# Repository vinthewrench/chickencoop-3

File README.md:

# Chicken Coop Controller 3.0

**Build your own automated, off-grid chicken coop door**

A minimal, ultra-reliable, battery-powered AVR controller that opens the door at sunrise, closes and locks it at sunset — completely offline, no sensors, no Wi-Fi, no cloud, no GPS.

Designed for a mobile pasture-raised coop that moves with cattle and sheep. Runs for months on a small 12 V battery (solar is only a top-up). Survives Arkansas mud, ice, dust, coyotes, and power failures.

Full 18-page design story, sunrise math, and lessons learned here:  
https://www.vinthewrench.com/<update this>

### Features

- True sunrise/sunset calculation using location + date (NO light sensor)
- Gravity-hung door with Progressive Automations PA-14 actuator
- Automatic locking bar (automotive-style actuator) to stop predators
- Manual override button with bi-color LED status
- Ultra-low sleep current (~355 µA) → months on a 7–22 Ah SLA/AGM battery
- One-time setup via serial console (no phone app or internet required)
- Two extra latching relays for electric fence or lights (zero holding current)
- Handles power failures, manual overrides, and reboots correctly
- Fully open-source (firmware + schematics + PCB)

### Licenses

- Firmware: MIT
- Hardware (schematics + PCB): CERN-OHL-P v2

You are free to study, modify, and build your own.

---

## How It Works

1. The DS3231M RTC wakes the ATmega1284P at the next event (sunrise or sunset).
2. Firmware calculates exact sunrise/sunset from latitude, longitude, and date.
3. If needed, it drives the door actuator and lock.
4. It sets the next alarm and goes back to deep sleep.

No drift, no false triggers from clouds, headlights, or moving the coop.

Manual button press overrides the schedule until the next natural event (sunrise/sunset). The system never fights you.

---

## Hardware

Custom 100 × 130 mm PCB (all through-hole friendly where possible).

### Major Components

| Component        | Part                          | Notes                                         |
| ---------------- | ----------------------------- | --------------------------------------------- |
| MCU              | ATmega1284P-PU (DIP-40)       | 128 KB flash, easy ISP, repairable            |
| RTC              | DS3231M                       | Integrated resonator, temperature compensated |
| Door Actuator    | Progressive Automations PA-14 | IP65, internal limits, stainless rod          |
| Lock Actuator    | 12 V automotive door lock     | Pulses only (200–300 ms)                      |
| Motor Drivers    | 2 × VNH7100BAS                | 15 A H-bridges with thermal copper pours      |
| 5 V Regulator    | Pololu D24V22F5               | High efficiency, low quiescent current        |
| Button           | Illuminated bi-color switch   | Red/Green status + override                   |
| Relays           | 2 × DSP1-L2-DC12V             | Latching (zero holding current)               |
| Relay Driver     | ULN2003A                      | Drives relays + optional loads                |
| Optional Console | SparkFun DEV-15096            | USB-to-serial for setup (removable)           |

Power: Single 12 V battery (SLA/AGM recommended). Direct 12 V to motors, regulated 5 V for logic.

---

## Firmware

Written in plain C for avr-gcc. No Arduino framework, no hidden magic.

Typical workflow:

```bash
cd firmware
make set-fuses
make
make flash          # or use your programmer
```

Full build system, clean targets, and EEPROM config handling included.

---

## Setup & Configuration

1. Flip the **CONFIG switch** to ON (this puts the controller into console mode).
2. Connect the optional SparkFun USB-to-serial module (or any 5 V TTL serial).
3. Open a terminal (38400 baud).
4. Set date/time, latitude, longitude, timezone offset, and schedule offsets.
5. Flip the **CONFIG switch** back to OFF when done.
6. Remove the module — the controller no longer needs it.

All settings stored in EEPROM. No re-configuration unless you move to a new location.

---

## Using the CONFIG Switch & Console

The physical **CONFIG switch** on the board toggles between normal low-power run mode and console configuration mode. When flipped to ON, the MCU stays awake, enables the serial console, and allows full setup/debug without sleeping. Flip back to OFF to resume automatic scheduling and deep sleep.

**Configuration steps:**

1. Flip CONFIG to ON.
2. Connect serial (38400 baud) and type commands.
3. Use `set` to configure, `event add` for schedules, `save` to commit.
4. Flip CONFIG to OFF.

**What you need to set (minimum for basic operation):**

- Date and time (`set date YYYY-MM-DD`, `set time HH:MM[:SS]`)
- Location (`set lat +/-DD.DDDD`, `set lon +/-DDD.DDDD`)
- Timezone (`set tz +/-HH`, `set dst on|off`)
- Events (`event add door on sunrise +0`, `event add door off sunset -15`, etc. for lock/relays)

**Key commands:**
| Command | What it does |
|----------------------------------|--------------|
| `help` | List all commands |
| `config` | Show current settings |
| `set date YYYY-MM-DD` | Set date |
| `set time HH:MM[:SS]` | Set time (local) |
| `set lat +/-DD.DDDD` | Set latitude |
| `set lon +/-DDD.DDDD` | Set longitude |
| `set tz +/-HH` | Set timezone offset |
| `set dst on\|off` | Enable/disable DST |
| `event add ...` | Add door open/close events (sunrise/sunset or fixed time) |
| `save` | Commit everything to EEPROM |
| `schedule` | Show today’s full schedule |
| `solar` | Show sunrise/sunset |
| `door open\|close\|toggle` | Manual door test |
| `lock engage\|release` | Manual lock test |

Type `help` for full list. Changes are RAM-only until `save`.

---

## Repository Contents

- /firmware/ — AVR source + Makefile
- /hardware/ — KiCad schematics + PCB layout

---

## Typical Daily Workflow (after initial setup)

The controller just works. You walk out once a day to collect eggs.

---

## Links & Resources

- Full article: https://www.vinthewrench.com/<update>
- Buy the exact actuator: Progressive Automations PA-14 (PA-01-12-56-N-12VDC model)

Questions? Open an issue or find me on X @vinthewrench.

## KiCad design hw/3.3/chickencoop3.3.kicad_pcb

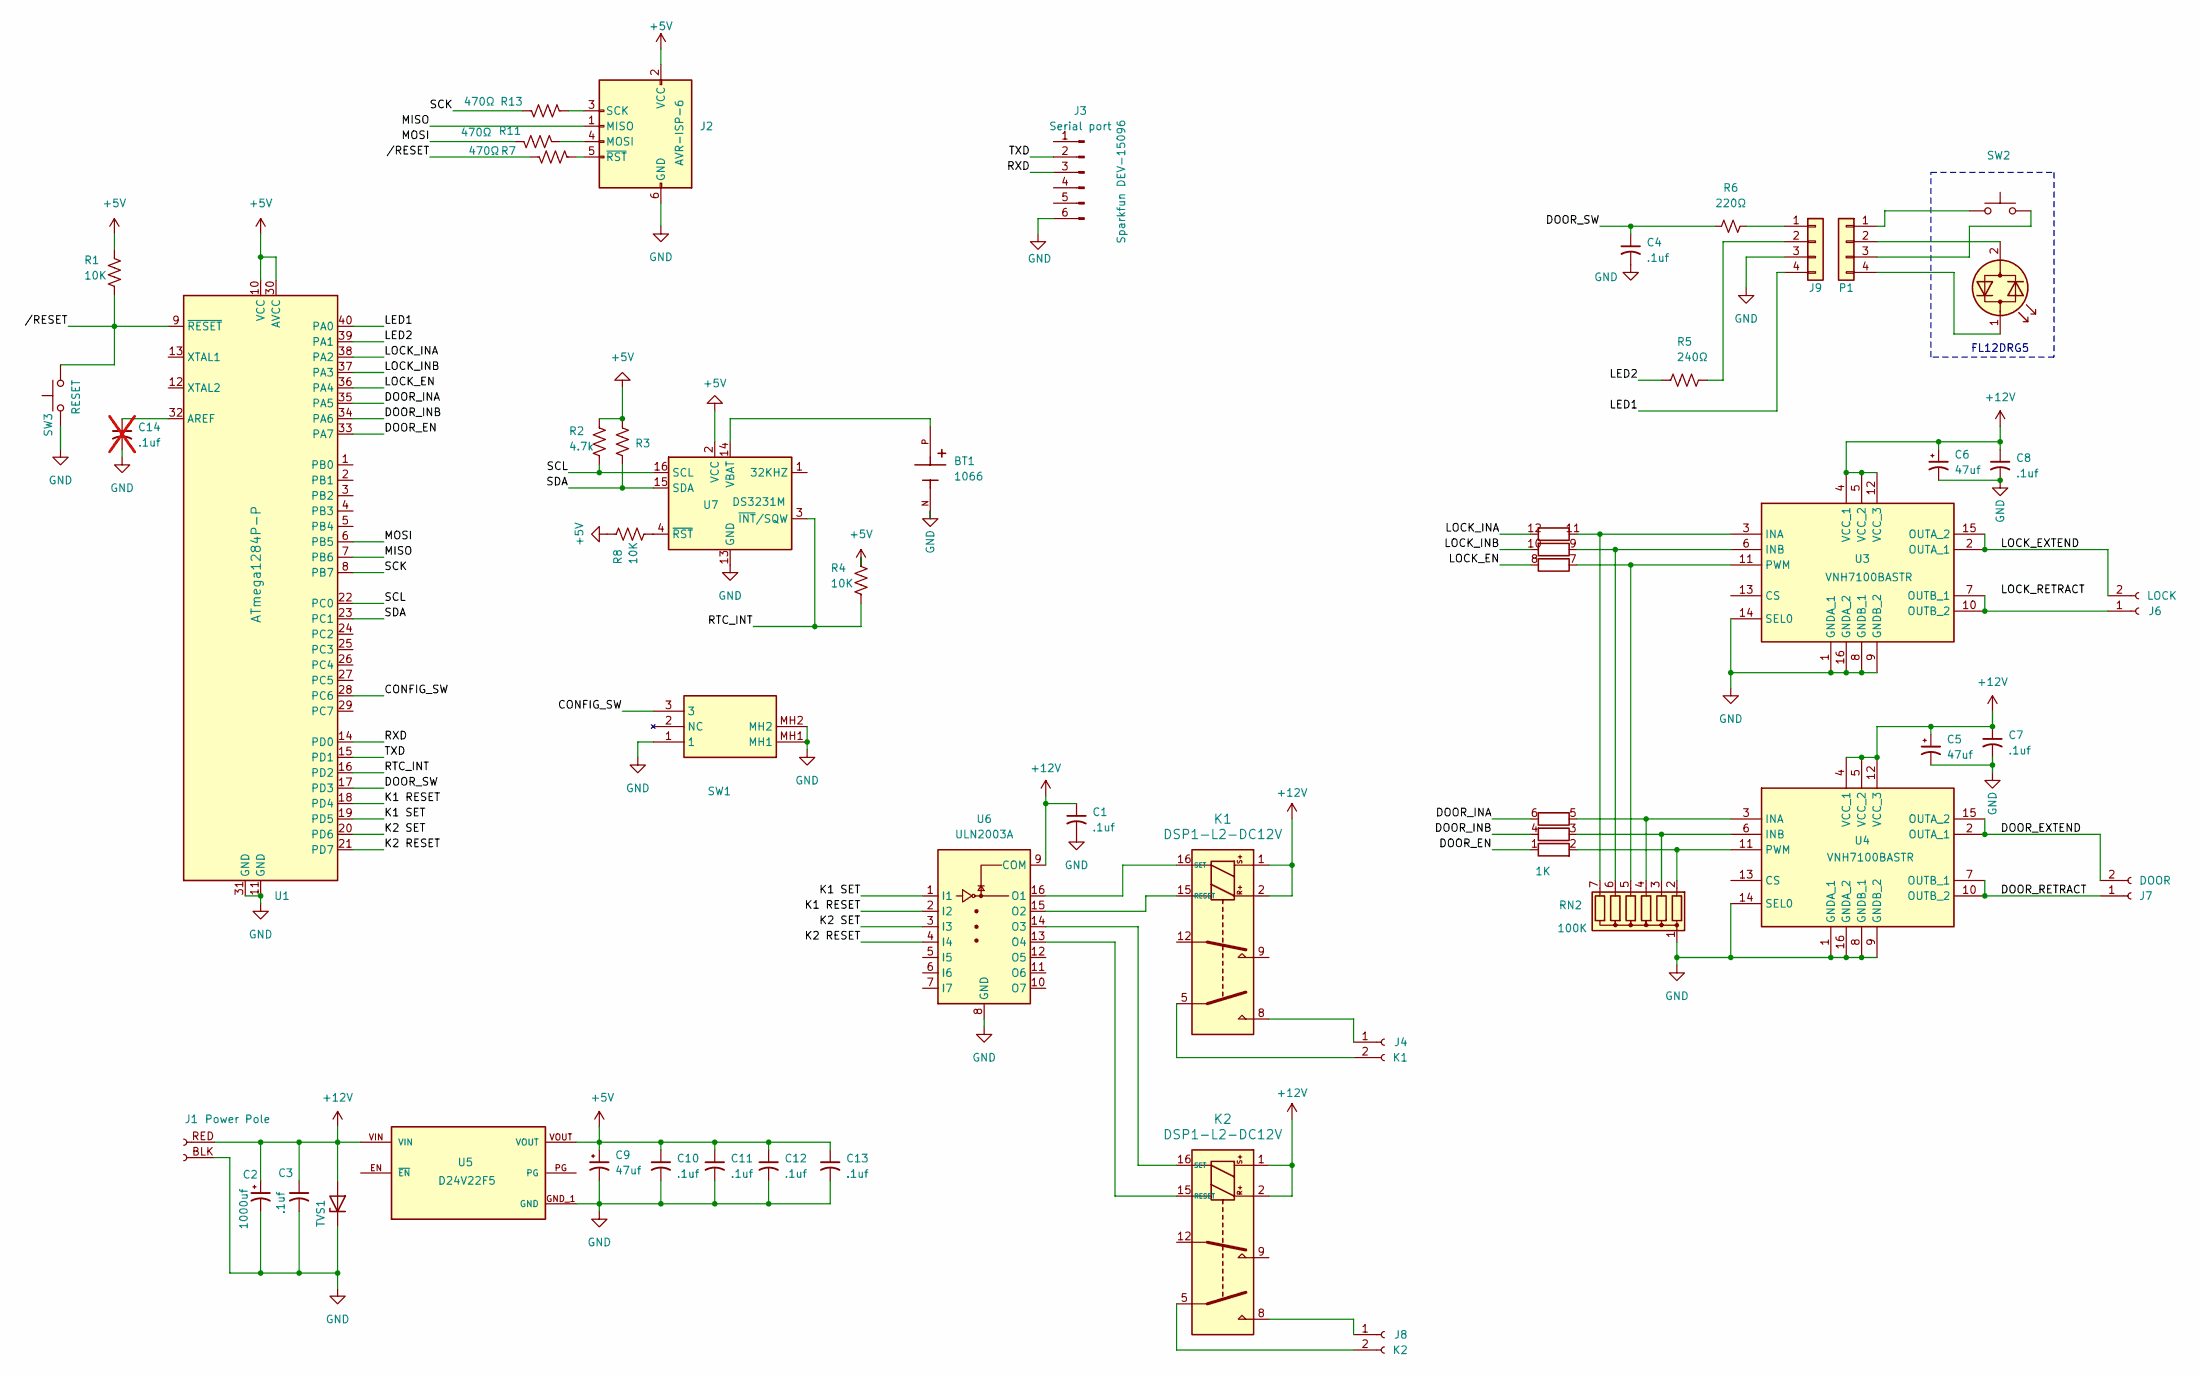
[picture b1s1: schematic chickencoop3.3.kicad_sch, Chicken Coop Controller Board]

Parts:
BT1: 1066; BAT_1066; PARTREV E
C1, C3, C4, C7, C8, C10, C11, C12, C13: .1uf; RCER71H104K0DBH03A
C2: 1000uf; CP_Radial_D10.0mm_P5.00mm
C5, C6, C9: 47uf; CP_Radial_D5.0mm_P2.00mm
C14: .1uf; RCER71H104K0DBH03A; not fitted
D1: LED_Dual_Bidirectional
J1: Power Pole; powerpole
J2: AVR-ISP-6; PinHeader_2x03_P2.54mm_Vertical
J3: Serial port; PinHeader_1x06_P2.54mm_Vertical
J4: K1; TerminalBlock_Phoenix_MKDS-1,5-2-5.08_1x02_P5.08mm_Horizont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
J6: LOCK; TerminalBlock_Phoenix_MKDS-1,5-2-5.08_1x02_P5.08mm_Horizont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
J7: DOOR; TerminalBlock_Phoenix_MKDS-1,5-2-5.08_1x02_P5.08mm_Horizont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
J8: K2; TerminalBlock_Phoenix_MKDS-1,5-2-5.08_1x02_P5.08mm_Horizont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
J9: Mini‑Fit Jr; Molex_Mini-Fit_Jr_5566-04A_2x02_P4.20mm_Vertical
K1, K2: DSP1-L2-DC12V
P1: Mini‑Fit Jr; Molex_Mini-Fit_Jr_5566-04A_2x02_P4.20mm_Vertical
R1, R4, R8: 10K; R_Axial_DIN0204_L3.6mm_D1.6mm_P7.62mm_Horizontal
R2: 4.7k; R_Axial_DIN0204_L3.6mm_D1.6mm_P7.62mm_Horizontal
R3: 4.7K; R_Axial_DIN0204_L3.6mm_D1.6mm_P7.62mm_Horizontal
R5: 240Ω; R_Axial_DIN0204_L3.6mm_D1.6mm_P7.62mm_Horizontal
R6: 220Ω; R_Axial_DIN0204_L3.6mm_D1.6mm_P7.62mm_Horizontal
R7, R11, R13: 470Ω; R_Axial_DIN0204_L3.6mm_D1.6mm_P7.62mm_Horizontal
RN2: 100K; R_Array_SIP7; Manufacturer_Part_Number 4607X-101-104LF
RN4: 1K; R_Array_SIP12; Manufacturer_Part_Number 4612X-102-102LF
SW1: SW_SPST; AS11CH; Mouser Part Number 633-AS11CH
SW2: SW_Push
SW3: RESET; SW_PUSH_6mm
TVS1: P6SMB18A; D_SMB_Handsoldering
U1: ATmega1284P-P; DIP-40_W15.24mm
U3, U4: VNH7100BASTR; SOIC127P600X175-16N; Manufacturer_Part_Number VNH7100BASTR; Mouser Part Number 511-VNH7100BASTR
U5: D24V22F5; MODULE_5V_2.5A_STEP-DOWN_D24V22F5; PARTREV 12 November 2015
U6: ULN2003A; DIP-16_W7.62mm
U7: DS3231M; SOIC-16W_7.5x10.3mm_P1.27mm

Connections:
+5V: C9.1, C10.1, C11.1, C12.1, C13.1, J2.2 (VCC), R1.1, R2.1, R3.1, R4.1, R8.1, U1.10 (VCC), U1.30 (AVCC), U5.VOUT, U7.2 (VCC)
+12V: C1.1, C2.1, C3.1, C5.1, C6.1, C7.1, C8.1, J1.RED, K1.1, K1.2, K2.1, K2.2, TVS1.2 (A), U3.4 (VCC_1), U3.5 (VCC_2), U3.12 (VCC_3), U4.4 (VCC_1), U4.5 (VCC_2), U4.12 (VCC_3), U5.VIN, U6.9 (COM)
/CONFIG_SW: SW1.3, U1.28 (PC6)
/DOOR_EN: RN4.1 (R1.1), U1.33 (PA7)
/DOOR_EXTEND: J7.2, U4.2 (OUTA_1), U4.15 (OUTA_2)
/DOOR_INA: RN4.6 (R3.2), U1.35 (PA5)
/DOOR_INB: RN4.4 (R2.2), U1.34 (PA6)
/DOOR_RETRACT: J7.1, U4.7 (OUTB_1), U4.10 (OUTB_2)
/DOOR_SW: C4.1, R6.1, U1.17 (PD3)
/K1 RESET: U1.18 (PD4), U6.2 (I2)
/K1 SET: U1.19 (PD5), U6.1 (I1)
/K2 RESET: U1.21 (PD7), U6.4 (I4)
/K2 SET: U1.20 (PD6), U6.3 (I3)
/LED1: J9.4, U1.40 (PA0)
/LED2: R5.1, U1.39 (PA1)
/LOCK_EN: RN4.8 (R4.2), U1.36 (PA4)
/LOCK_EXTEND: J6.2, U3.2 (OUTA_1), U3.15 (OUTA_2)
/LOCK_INA: RN4.12 (R6.2), U1.38 (PA2)
/LOCK_INB: RN4.10 (R5.2), U1.37 (PA3)
/MISO: J2.1 (MISO), U1.7 (PB6)
/MOSI: R11.1, U1.6 (PB5)
/RTC_INT: R4.2, U1.16 (PD2), U7.3 (~INT/SQW)
/RXD: J3.3, U1.14 (PD0)
/SCK: R13.1, U1.8 (PB7)
/SCL: R2.2, U1.22 (PC0), U7.16 (SCL)
/SDA: R3.2, U1.23 (PC1), U7.15 (SDA)
/TXD: J3.2, U1.15 (PD1)
//RESET: R1.2, R7.1, SW3.2, U1.9 (~RESET)
GND: BT1.N, C1.2, C2.2, C3.2, C4.2, C5.2, C6.2, C7.2, C8.2, C9.2, C10.2, C11.2, C12.2, C13.2, C14.2, J1.BLK, J2.6 (GND), J3.6, J9.3, RN2.1 (common), SW1.1, SW1.MH1, SW1.MH2, SW3.1, TVS1.1 (K), U1.11 (GND), U1.31 (GND), U3.1 (GNDA_1), U3.8 (GNDB_1), U3.9 (GNDB_2), U3.14 (SEL0), U3.16 (GNDA_2), U4.1 (GNDA_1), U4.8 (GNDB_1), U4.9 (GNDB_2), U4.14 (SEL0), U4.16 (GNDA_2), U5.GND_1 (GND), U5.GND_2 (GND), U6.8 (GND), U7.5 (GND), U7.6 (GND), U7.7 (GND), U7.8 (GND), U7.9 (GND), U7.10 (GND), U7.11 (GND), U7.12 (GND), U7.13 (GND)
unnamed: D1.1 (KA), P1.4
unnamed: D1.2 (AK), P1.2
unnamed: J2.4 (MOSI), R11.2
unnamed: J2.3 (SCK), R13.2
unnamed: J2.5 (~RST), R7.2
unnamed: J4.1, K1.8
unnamed: J4.2, K1.5
unnamed: J6.1, U3.7 (OUTB_1), U3.10 (OUTB_2)
unnamed: J8.1, K2.8
unnamed: J8.2, K2.5
unnamed: J9.1, R6.2
unnamed: J9.2, R5.2
unnamed: K1.15 (RESET), U6.15 (O2)
unnamed: K1.16 (SET), U6.16 (O1)
unnamed: K2.15 (RESET), U6.13 (O4)
unnamed: K2.16 (SET), U6.14 (O3)
unnamed: P1.1, SW2.1
unnamed: P1.3, SW2.2
unnamed: RN2.2 (R1), RN4.2 (R1.2), U4.11 (PWM)
unnamed: RN2.3 (R2), RN4.3 (R2.1), U4.6 (INB)
unnamed: RN2.4 (R3), RN4.5 (R3.1), U4.3 (INA)
unnamed: RN2.5 (R4), RN4.7 (R4.1), U3.11 (PWM)
unnamed: RN2.6 (R5), RN4.9 (R5.1), U3.6 (INB)
unnamed: RN2.7 (R6), RN4.11 (R6.1), U3.3 (INA)
unnamed: C14.1, U1.32 (AREF)
unnamed: BT1.P, U7.14 (VBAT)
unnamed: R8.2, U7.4 (~RST)

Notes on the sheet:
FL12DRG5

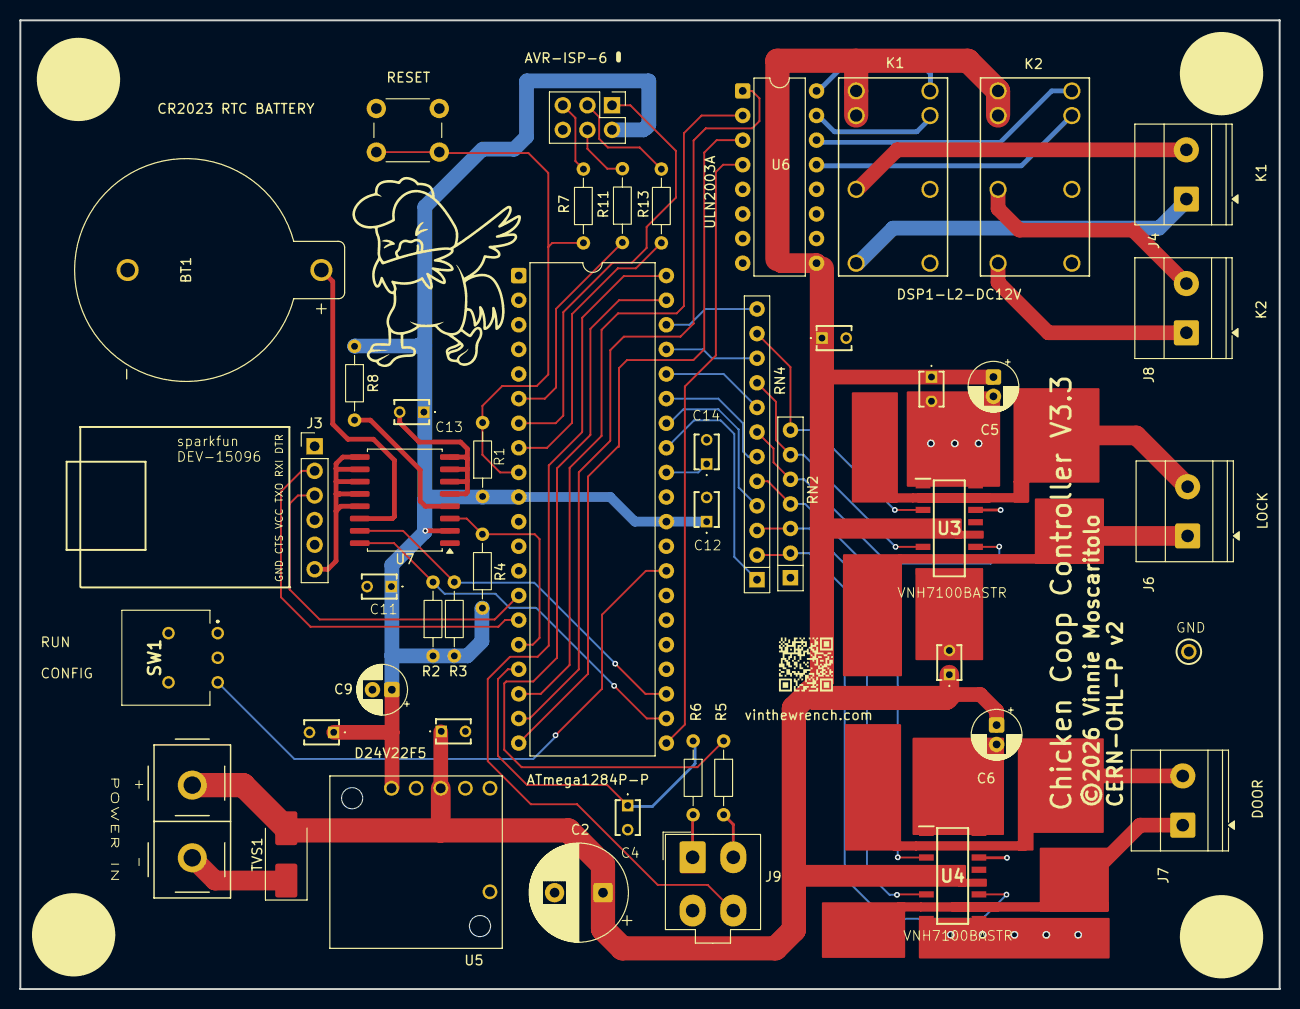
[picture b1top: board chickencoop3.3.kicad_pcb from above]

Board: 2 copper layers, 130.0 x 100.0 mm, 47 parts (0 on the bottom side), 52 nets.

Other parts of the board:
TP3: GND; 5000

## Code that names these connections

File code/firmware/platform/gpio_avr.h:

/*
 * gpio_avr.h
 *
 * Project: Chicken Coop Controller
 * Purpose: AVR GPIO pin definitions and low-level hardware mapping
 *
 * This header defines the canonical mapping between AVR GPIO pins
 * and physical hardware functions on the Chicken Coop Controller PCB.
 *
 * IMPORTANT DESIGN RULES:
 *  - All mappings in this file are LOCKED to the board schematic.
 *  - Do NOT rename, repurpose, or reassign any pin here unless
 *    the PCB schematic and layout are changed accordingly.
 *  - Higher-level code MUST treat these as hardware truth.
 *
 * SAFETY NOTE:
 *  - Several pins in this file control motors, relays, and solenoids.
 *  - Incorrect initialization or prolonged activation CAN damage hardware.
 *  - All outputs must be initialized to a known-safe OFF state at boot.
 *
 * Updated:
 *   (fill in date when pin mapping changes — not for code-only edits)
 */

#pragma once

/* --------------------------------------------------------------------------
 * Status LED Outputs
 * --------------------------------------------------------------------------
 *
 * These pins drive the front-panel red/green status LED through
 * external driver hardware.
 *
 * Naming convention:
 *  - LED_IN1 / LED_IN2 match the schematic net names.
 *  - Color association is documented for human clarity only.
 *
 * NOTE:
 *  - Do NOT change these names unless the hardware wiring changes.
 * -------------------------------------------------------------------------- */
 #define LED_IN1_BIT   PA1   /* RED   */
 #define LED_IN2_BIT   PA0   /* GREEN */

/* --------------------------------------------------------------------------
 * Door Motor H-Bridge Control (VNH7100BASTR)
 * --------------------------------------------------------------------------
 *
 * This H-bridge drives the main chicken coop door actuator.
 *
 * Electrical notes:
 *  - The door actuator includes internal end-of-travel limit switches.
 *  - Despite this, firmware MUST still enforce a maximum travel time
 *    as a fail-safe against wiring or switch failure.
 *
 * Pin behavior:
 *  - DOOR_EN   : Enables/disables the H-bridge (active HIGH)
 *  - DOOR_INA  : Direction control A
 *  - DOOR_INB  : Direction control B
 *
 * Reset behavior:
 *  - DOOR_EN MUST be driven LOW at boot.
 *  - INA/INB MUST be driven LOW at boot.
 *
 * -------------------------------------------------------------------------- */
/* DOOR_INA -> PF5 (physical pin 38) */
/* DOOR_INB -> PF6 (physical pin 37) */
/* DOOR_EN  -> PF7 (physical pin 36) */
#define DOOR_INA_BIT   PA5
#define DOOR_INB_BIT   PA6
#define DOOR_EN_BIT    PA7

/* --------------------------------------------------------------------------
 * Door Lock Actuator H-Bridge (VNH7100BASTR)
 * --------------------------------------------------------------------------
 *
 * This H-bridge drives the door LOCK actuator.
 *
 * CRITICAL SAFETY WARNING:
 *  - The lock actuator does NOT have end-of-travel limit switches.
 *  - It MUST be driven using a SHORT, FIXED-DURATION PULSE ONLY.
 *  - Continuous drive WILL overheat and destroy the actuator.
 *
 * Firmware requirements:
 *  - LOCK_EN MUST never be left asserted continuously.
 *  - A hard maximum pulse time (lock_pulse_ms) is mandatory.
 *  - Lock control must be edge-triggered, not state-held.
 *
 * JTAG NOTE:
 *  - LOCK_EN uses PF4, which is a JTAG pin by default.
 *  - Runtime JTAG disable is REQUIRED before driving this pin.
 * -------------------------------------------------------------------------- */
/* LOCK_INA -> PF0 */
/* LOCK_INB -> PF1 */
/* LOCK_EN  -> PF4 */
#define LOCK_INA_BIT   PA2
#define LOCK_INB_BIT   PA3
#define LOCK_EN_BIT    PA4

/* --------------------------------------------------------------------------
 * Latching Relay Outputs
 * --------------------------------------------------------------------------
 *
 * These pins drive a dual latching relay via external driver circuitry.
 *
 * Relay behavior:
 *  - SET and RESET are separate coils.
 *  - Coils must be pulsed briefly; they must NOT be held energized.
 *
 * Firmware requirements:
 *  - All relay outputs must default to OFF at boot.
 *  - Pulse duration must be limited in software.
 * -------------------------------------------------------------------------- */
#define RELAY1_SET_BIT    PD5
#define RELAY1_RESET_BIT  PD4
#define RELAY2_SET_BIT    PD6
#define RELAY2_RESET_BIT  PD7


/* --------------------------------------------------------------------------
 * Configuration Mode Slide Switch
 * --------------------------------------------------------------------------
 *
 * Electrical behavior (LOCKED):
 *  - Switch OPEN    → PC6 pulled HIGH → CONFIG MODE
 *  - Switch CLOSED  → PC6 tied to GND  → NORMAL MODE
 *
 * Firmware requirements:
 *  - Pin configured as INPUT
 *  - Internal pull-up enabled
 *  - Logic is ACTIVE-HIGH for CONFIG
 *
 * Read example:
 *   bool config_mode = (PINC & (1u << CONFIG_SW_BIT)) != 0;
 * -------------------------------------------------------------------------- */
#define CONFIG_SW_BIT   PC6


#define DOOR_SW_BIT     PD3


#define RTC_INT_BIT     PD2



/* --------------------------------------------------------------------------
 * GPIO Initialization
 * --------------------------------------------------------------------------
 *
 * coop_gpio_init():
 *  - Configures all actuator-related pins as outputs
 *  - Forces a known-safe OFF state on all drivers
 *
 * This function MUST be called:
 *  - At the very start of main()
 *  - Before any scheduler, state machine, or interrupt enables
 *
 * Failure to do so can result in:
 *  - Motors energizing unexpectedly
 *  - Solenoids overheating
 *  - Hardware damage
 * -------------------------------------------------------------------------- */
void coop_gpio_init(void);


/* --------------------------------------------------------------------------
 * External Wake Inputs (INT0 / INT1)
 * -------------------------------------------------------------------------- */

static inline void gpio_rtc_int_input_init(void)
{
    /* RTC_INT uses external pull-up */
    DDRD  &= (uint8_t)~(1u << RTC_INT_BIT);
    PORTD &= (uint8_t)~(1u << RTC_INT_BIT);
}

static inline void gpio_door_sw_input_init(void)
{
    /* Door switch uses internal pull-up */
    DDRD  &= (uint8_t)~(1u << DOOR_SW_BIT);
    PORTD |=  (uint8_t)(1u << DOOR_SW_BIT);
}

static inline uint8_t gpio_rtc_int_is_asserted(void)
{
    return (PIND & (1u << RTC_INT_BIT)) == 0u;
}

static inline uint8_t gpio_door_sw_is_asserted(void)
{
    return (PIND & (1u << DOOR_SW_BIT)) == 0u;
}

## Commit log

2025-12-30 Console scheduler validation: RTC set/save, solar times, and schedule intent confirmed
2025-12-30 CLI: finalize explicit event grammar, persistence, and resolver
    - Make config the sole authoritative event store
    - Add explicit solar/civil anchors (sunrise/sunset, dawn/dusk)
    - Support implicit midnight for bare HH:MM
    - Fix command arg limits for extended grammar
    - Add # comment stripping before tokenization
    - Remove device-invented default events (door)
2025-12-31 ignore coop.cfg
2025-12-31 Stop tracking coop.cfg
2026-01-01 cleaning up devices
2026-01-02 Bring-up checkpoint: door/lock HW abstraction, host parity, console test hooks
    - Introduce door_hw / lock_hw hardware abstraction using INA/INB/EN model
    - Add AVR implementations for door and lock H-bridge control
    - Add host-side equivalents for hardware simulation
    - Keep console test hooks (door open/close, lock engage/release) as temporary stubs
    - Device path (door_device) drives hardware directly for now
    - Preserve separation between device intent and console imperative testing
2026-01-05 led-console-debug
2026-01-08 Refactor door control into explicit state machines; integrate lock and LED logic
    - Introduced platform-agnostic door and lock state machines
    - Enforced unlock-before-move and lock-after-close sequencing
    - Added LED state machine with OFF / ON / BLINK / BREATHE-PULSE modes
    - Centralized door motion transitions to drive LED behavior deterministically
    - Removed hardware timing and safety logic from door device layer
    - Added host-side hardware stubs for visibility and debugging
2026-01-18 more consolidation
2026-01-18 fix console and version
2026-02-04 Update firmware for V3.2 hardware bring-up
2026-02-04 Simplify door lock: remove lock state machine, add bounded blocking lock pulse
    - Replace async lock state machine with blocking door_lock driver
    - Enforce hard max lock pulse time at hardware layer
    - Simplify door state machine sequencing (unlock → move → settle → lock)
    - Remove redundant lock device and host/AVR abstractions
    - Preserve host/firmware parity
2026-02-04 some hardware testing
2026-02-04 added lock_settle_ms - time after unlock before motion
2026-02-04 cleanup add event syntax
2026-02-05 Fix RTC issues and remove uptime-based time staging
2026-02-06 RTC epoch + EESAVE fuse preserve + mini_printf 32-bit support
2026-02-09 LED action takes count argument -- sleep test works
2026-02-10 some documentation updates
2026-02-10 added test for door sw
2026-02-10 door toggle code
2026-02-11 BOD and RTC fixes
2026-02-11 minimal door button hookup in console mode
2026-02-12 removed all HOST cruft - now that we have hardware
2026-02-16 added cppcheck to makefile
2026-02-16 updated RTC to run as UTC
2026-02-16 minor textual cleanup
2026-02-17 FIX times display - always show local
2026-02-17 scedule bug fixed
2026-02-17 allow time entry as h:ss an hh:ss
2026-02-17 cave man level autocomplete with <tab>
2026-02-19 Remove AI induced retarted programming
2026-02-19 prettier LED pulse
2026-02-19 relay_device: add manual override concept using UTC timestamp to suppress stale schedule events
2026-02-20 added code for DS3231
2026-02-20 updated HW to use DS3231
2026-03-02 switched RTC to DS3231
2026-03-04 added schematic
2026-03-05 fix makefile comment
2026-03-05 Fix scheduler next-event logic and pass current minute
    scheduler_next_event_minute() previously returned the earliest event
    minute in the table regardless of current time. This caused incorrect
    behavior when querying the next event from the console or sleep logic.
    The scheduler now receives the current UTC minute-of-day and returns
    the earliest event strictly after the current time. If no future event
    exists today, it wraps to the earliest event tomorrow.
2026-03-05 clean garbage
2026-06-02 Ignore KiCad footprint cache

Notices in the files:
hw/3.3/chickencoop3.3.kicad_pcb:
©2026 Vinnie Moscaritolo
CERN-OHL-P v2
hw/3.3/chickencoop3.3.kicad_sch:
CERN-OHL-P v2 Permissive Open Hardware Licence
